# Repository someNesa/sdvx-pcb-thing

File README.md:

# sdvx-pcb-thing
 a sad attempt at an sdvx controller pcb

with help from:

https://wiki.ai03.com/books/pcb-design/chapter/pcb-designer-guide

https://www.masterzen.fr/2020/05/03/designing-a-keyboard-part-1/

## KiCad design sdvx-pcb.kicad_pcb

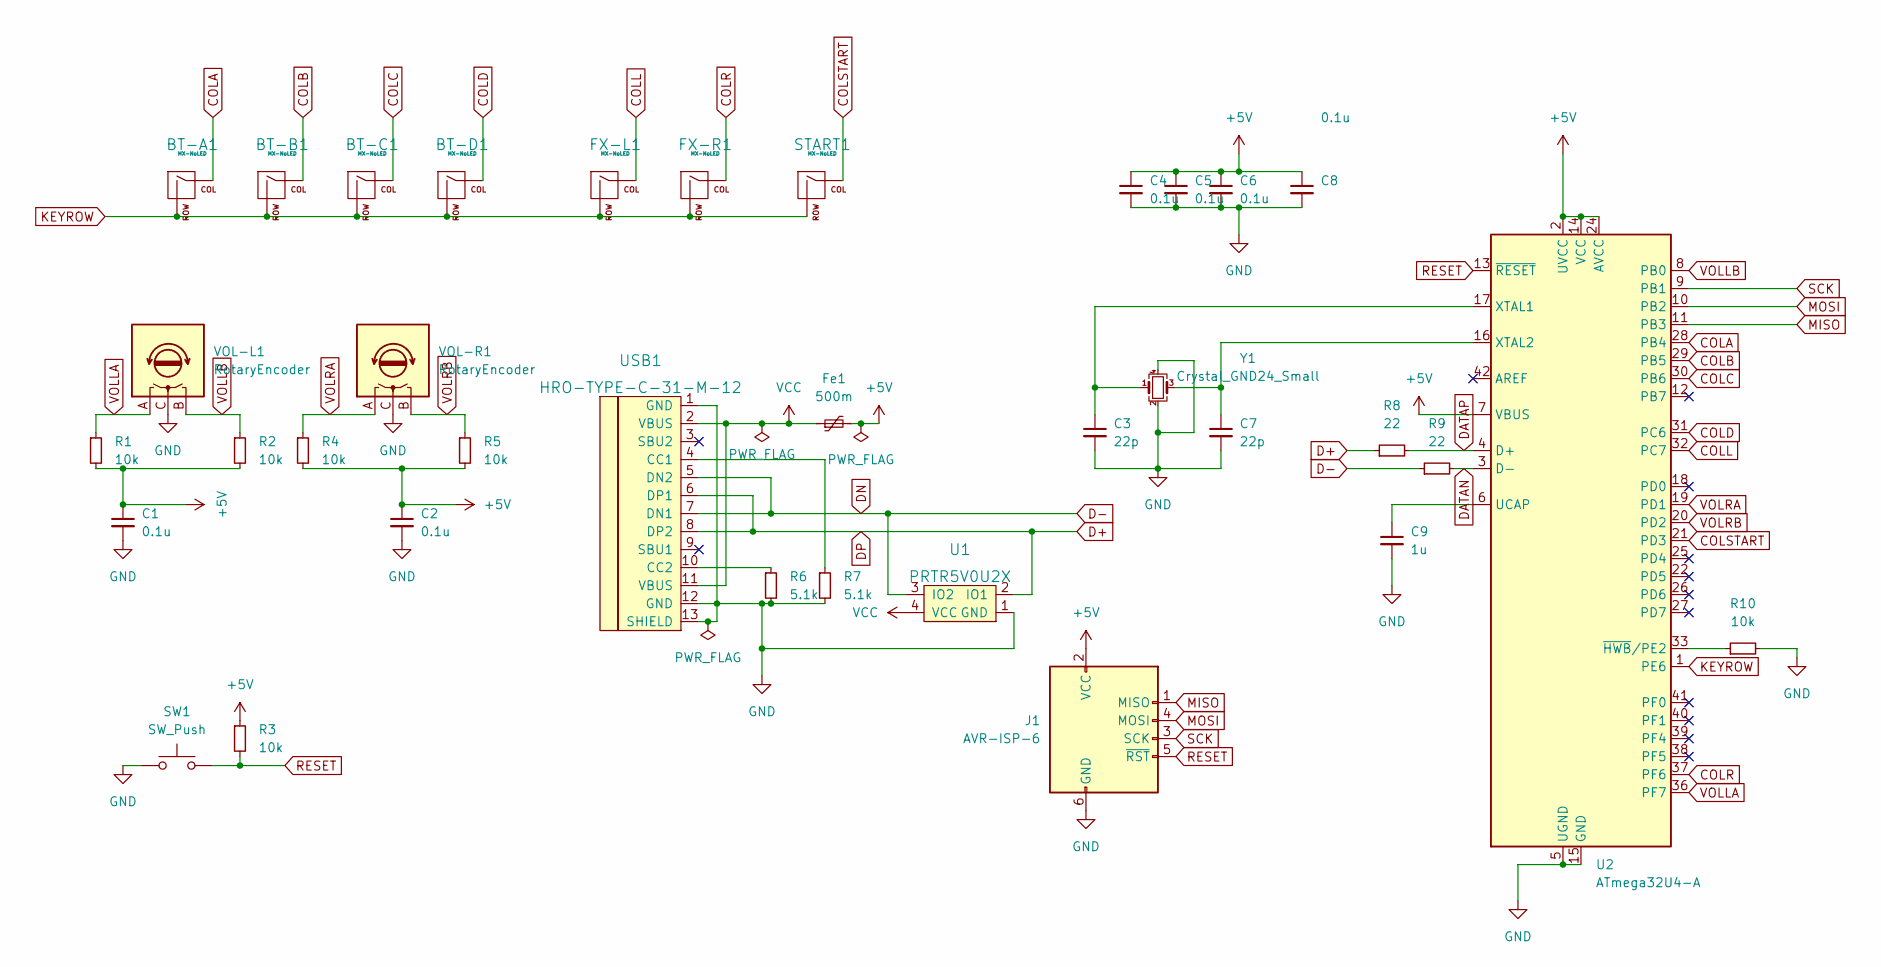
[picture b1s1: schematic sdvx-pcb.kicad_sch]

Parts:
BT-A1: MX-NoLED; MXOnly-1.5U-Hotswap
BT-B1: MX-NoLED; MXOnly-1.5U-Hotswap
BT-C1: MX-NoLED; MXOnly-1.5U-Hotswap
BT-D1: MX-NoLED; MXOnly-1.5U-Hotswap
C1, C2, C4, C5, C6, C8: 0.1u; C_0805_2012Metric_Pad1.18x1.45mm_HandSolder
C3, C7: 22p; C_0805_2012Metric_Pad1.18x1.45mm_HandSolder
C9: 1u; C_0805_2012Metric_Pad1.18x1.45mm_HandSolder
FX-L1: MX-NoLED; MXOnly-2.25U-Hotswap
FX-R1: MX-NoLED; MXOnly-2.25U-Hotswap
Fe1: 500m; Fuse_1206_3216Metric_Pad1.42x1.75mm_HandSolder
J1: AVR-ISP-6; Reset_Pretty-Mask
R1, R2, R3, R4, R5, R10: 10k; R_0805_2012Metric_Pad1.20x1.40mm_HandSolder
R6, R7: 5.1k; R_0805_2012Metric_Pad1.20x1.40mm_HandSolder
R8, R9: 22; R_0805_2012Metric_Pad1.20x1.40mm_HandSolder
START1: MX-NoLED; MXOnly-1U-Hotswap
SW1: SW_Push; SW_SPST_SKQG_WithStem
U1: PRTR5V0U2X; SOT143B
U2: ATmega32U4-A; TQFP-44_10x10mm_P0.8mm
USB1: HRO-TYPE-C-31-M-12; HRO-TYPE-C-31-M-12-HandSoldering
VOL-L1: RotaryEncoder; RotaryEncoder_Alps_EC11E_Vertical_H20mm_CircularMountingHol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
VOL-R1: RotaryEncoder; RotaryEncoder_Alps_EC11E_Vertical_H20mm_CircularMountingHol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
Y1: Crystal_GND24_Small; Crystal_SMD_3225-4Pin_3.2x2.5mm_HandSoldering

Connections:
+5V: C1.1, C2.1, C4.1, C5.1, C6.1, C8.1, Fe1.2, J1.2 (VCC), R1.2, R2.2, R3.1, R4.2, R5.2, U2.2 (UVCC), U2.7 (VBUS), U2.14 (VCC), U2.24 (AVCC), U2.34 (VCC), U2.44 (AVCC)
COLA: BT-A1.1 (COL), U2.28 (PB4)
COLB: BT-B1.1 (COL), U2.29 (PB5)
COLC: BT-C1.1 (COL), U2.30 (PB6)
COLD: BT-D1.1 (COL), U2.31 (PC6)
COLL: FX-L1.1 (COL), U2.32 (PC7)
COLR: FX-R1.1 (COL), U2.37 (PF6)
COLSTART: START1.1 (COL), U2.21 (PD3)
D+: R8.1, U1.2 (IO1), USB1.6 (DP1), USB1.8 (DP2)
D-: R9.1, U1.3 (IO2), USB1.5 (DN2), USB1.7 (DN1)
DATAN: R9.2, U2.3 (D-)
DATAP: R8.2, U2.4 (D+)
GND: C1.2, C2.2, C3.2, C4.2, C5.2, C6.2, C7.2, C8.2, C9.2, J1.6 (GND), R6.2, R7.2, R10.2, SW1.1, U1.1 (GND), U2.5 (UGND), U2.15 (GND), U2.23 (GND), U2.35 (GND), U2.43 (GND), USB1.1 (GND), USB1.12 (GND), USB1.13 (SHIELD), VOL-L1.C, VOL-R1.C, Y1.2, Y1.4
KEYROW: BT-A1.2 (ROW), BT-B1.2 (ROW), BT-C1.2 (ROW), BT-D1.2 (ROW), FX-L1.2 (ROW), FX-R1.2 (ROW), START1.2 (ROW), U2.1 (PE6)
MISO: J1.1 (MISO), U2.11 (PB3)
MOSI: J1.4 (MOSI), U2.10 (PB2)
unnamed: C3.1, U2.17 (XTAL1), Y1.1
unnamed: C7.1, U2.16 (XTAL2), Y1.3
unnamed: C9.1, U2.6 (UCAP)
unnamed: R6.1, USB1.10 (CC2)
unnamed: R7.1, USB1.4 (CC1)
unnamed: R10.1, U2.33 (~HWB/PE2)
RESET: J1.5 (~RST), R3.2, SW1.2, U2.13 (~RESET)
SCK: J1.3 (SCK), U2.9 (PB1)
VCC: Fe1.1, U1.4 (VCC), USB1.2 (VBUS), USB1.11 (VBUS)
VOLLA: R1.1, U2.36 (PF7), VOL-L1.A
VOLLB: R2.1, U2.8 (PB0), VOL-L1.B
VOLRA: R4.1, U2.19 (PD1), VOL-R1.A
VOLRB: R5.1, U2.20 (PD2), VOL-R1.B

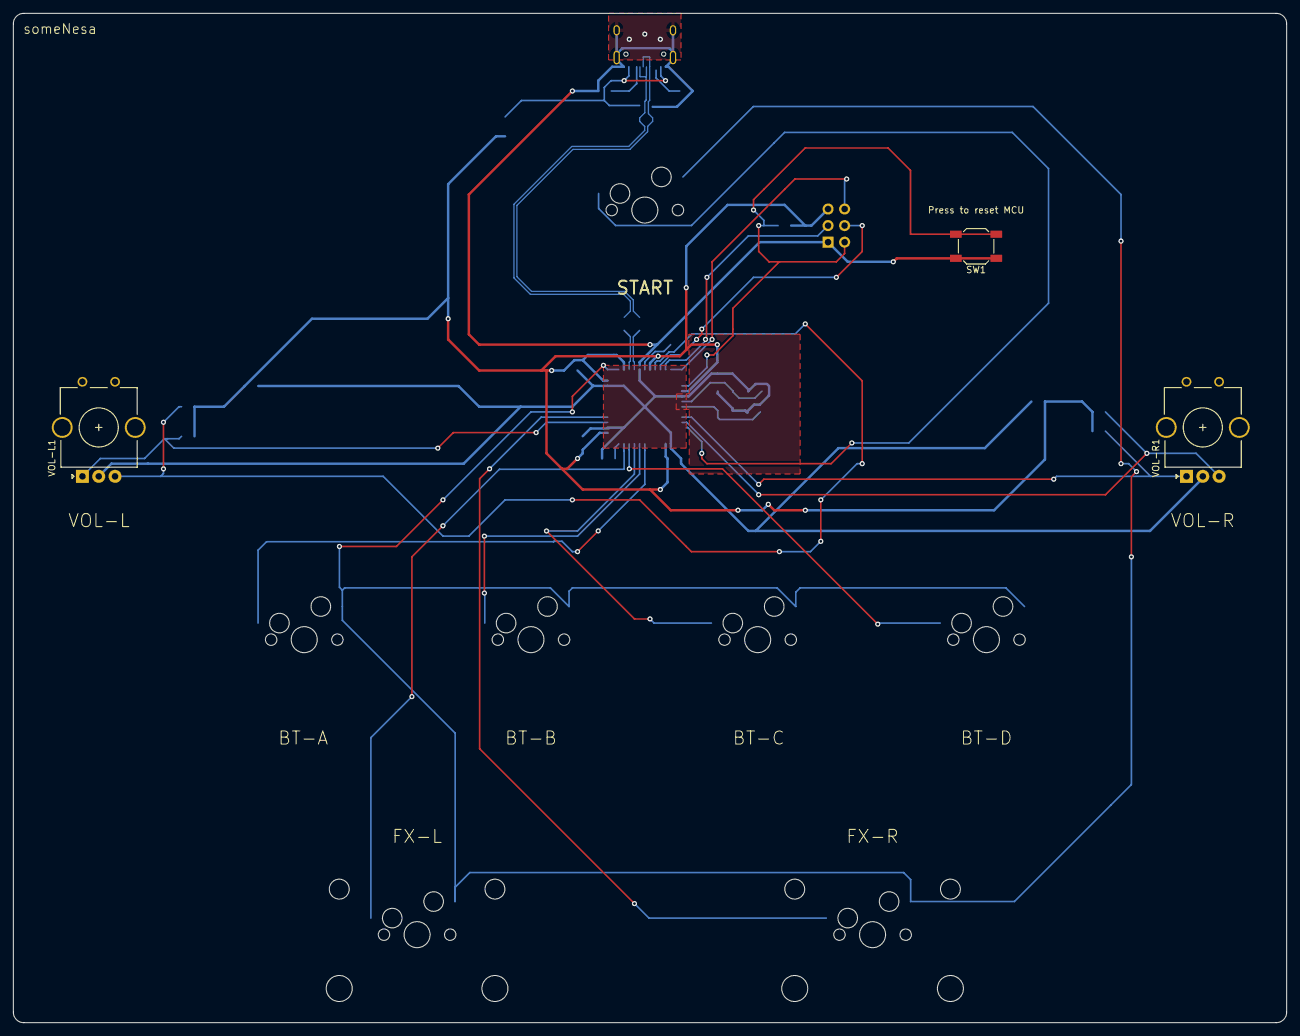
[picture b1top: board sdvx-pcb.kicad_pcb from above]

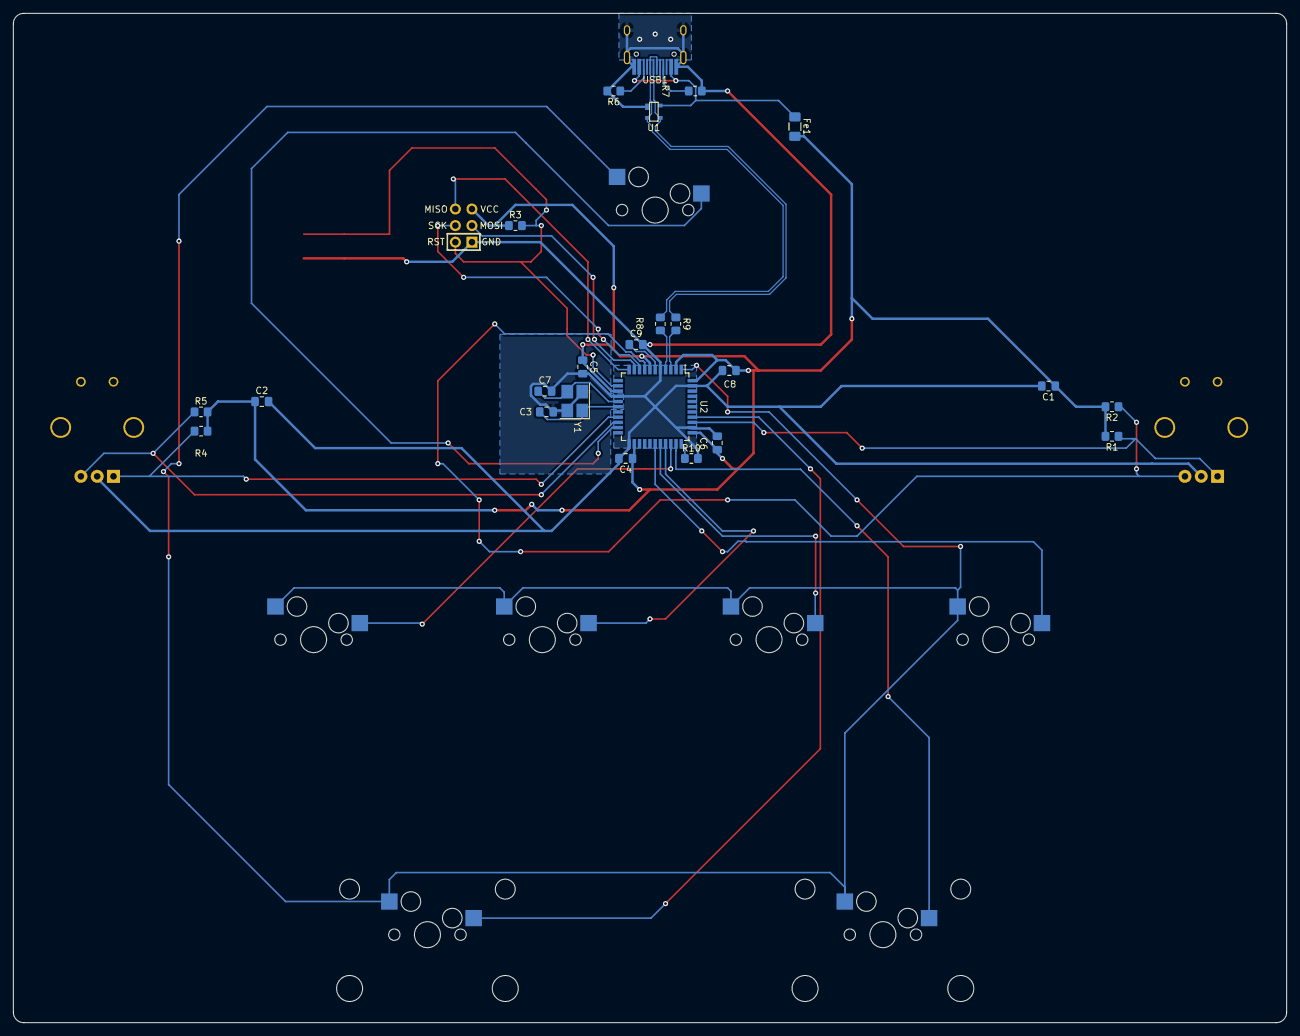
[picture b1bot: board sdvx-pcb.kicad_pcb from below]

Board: 2 copper layers, 195.3 x 154.8 mm, 35 parts (25 on the bottom side), 29 nets.

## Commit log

2022-06-06 project create
    create project
2022-06-06 add submodules
2022-06-06 add libraries
    add libraries
2022-06-06 edits
    edits
2022-06-06 some edits
    some edits
2022-06-06 more edits
    more edits
2022-06-06 hmm
    hmmm
2022-06-07 schematic finish
    finished schematic maybe
2022-06-07 pcb start
    start pcb
2022-06-07 i shouldnt have used kicad
    mistakes
2022-06-07 spaghetti
    w
2022-06-07 done?
    done?
2022-06-07 gerber
    gerber
2022-06-07 rotary encoders
    sike not done
2022-06-07 gerber again
    gerbers
2022-06-07 zip
    zip
2022-06-08 where the grounds
    WHERE
2022-06-08 finish
    finish?
